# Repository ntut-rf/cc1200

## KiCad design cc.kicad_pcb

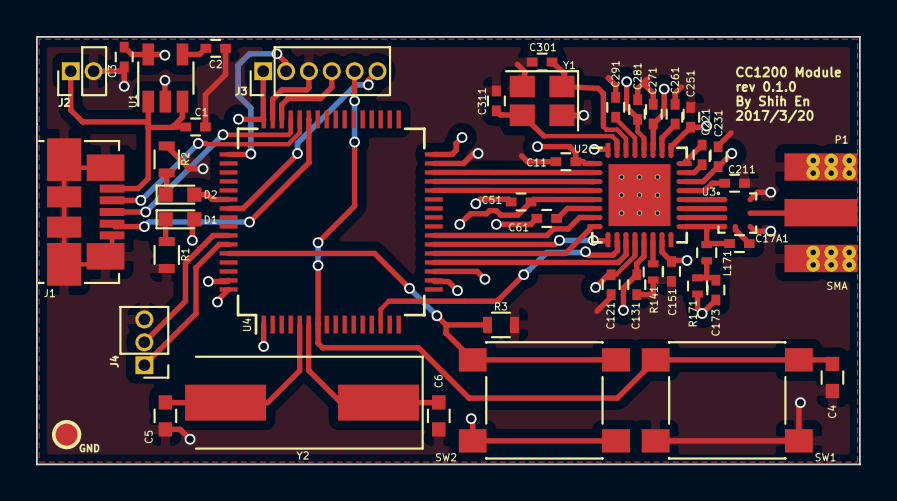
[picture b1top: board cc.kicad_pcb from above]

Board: 4 copper layers, 45.7 x 23.7 mm, 46 parts (0 on the bottom side), 43 nets.

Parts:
C1: 0.1uF; C_0402
C2: 0.01uF; C_0402
C3: 2.2uF; C_0402
C4: 0.1uF/25V; C_0603
C5, C6: 20pF; C_0603
C11, C51, C121, C131, C151, C221, C251, C261, C271, C281, C291: 47nF; C_0402
C17A1: 100pF; C_0402
C61: 220nF; C_0402
C173: 56pF; C_0402
C211: 10nF; C_0402
C231: 1.5nF; C_0402
C301, C311: 15pF; C_0402
D1: LED_PWR; LED_0603
D2: LED_TEST; LED_0603
GND: GND; TESTPOINT-50MIL
J1: USB_OTG; USB_Micro-B_Molex_47346-0001
J2: CONN_PWR; Pin_Header_Straight_1x02_Pitch1.27mm
J3: CONN_DEBUG; Pin_Header_Straight_1x06_Pitch1.27mm
J4: CONN_USART; Pin_Header_Straight_1x03_Pitch1.27mm
L171: 56nH; L_0402
P1: SMA; SMA-EDGE
R1, R2: 200; R_0603
R3: 10k; R_0603
R141: 56k; R_0402
R171: 18; R_0402
SW1, SW2: SW_Push; SW_SPST_PTS645
U1: TPS79333; TSOT-23-5
U2: CC1200
U3: BALF-112X-02D3
U4: STM32L475RC; LQFP-64_10x10mm_Pitch0.5mm
Y1: 40MHz; NX3225SA-40M-EXS00A-CS03880
Y2: 8MHz(16pF); Crystal_SMD_HC49-SD

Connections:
+5V: C1.1, J1.1, J2.1, U1.1, U1.3
CC_GPIO0: U2.10, U4.14
CC_GPIO2: U2.4, U4.28
CC_GPIO3: U2.3, U4.29
CC_MISO: U2.9, U4.22
CC_MOSI: U2.7, U4.23
CC_NSS: U2.11, U4.20
CC_RESET_N: U2.2, U4.30
CC_SCLK: U2.8, U4.21
GND: C1.2, C2.2, C3.2, C4.1, C5.2, C6.2, C11.2, C51.2, C61.2, C121.2, C131.2, C151.2, C211.2, C221.2, C251.2, C261.2, C271.2, C281.2, C291.2, C301.2, C311.2, J1.5, J1.6, J2.2, J3.3, J4.3, P1.2, R1.2, R2.1, R3.2, R141.2, SW1.2, U1.2, U2.32, U2.33, U3.A1, U3.E1, U4.18, U4.31, U4.47, U4.63, Y1.2, Y1.4
NRST: C4.2, J3.5, SW1.1, U4.7
unnamed: C2.1, U1.4
unnamed: C5.1, U4.5, Y2.2
unnamed: C6.1, U4.6, Y2.1
unnamed: C17A1.1, L171.1, U2.17, U3.E3
unnamed: C17A1.2, U3.E2
unnamed: C61.1, U2.6
unnamed: C173.1, L171.2, R171.1
unnamed: C211.1, U2.21
unnamed: C231.1, U2.24
unnamed: C231.2, U2.23
unnamed: C261.1, U2.26
unnamed: C291.1, U2.29
unnamed: C301.1, U2.30, Y1.1
unnamed: C311.1, U2.31, Y1.3
unnamed: D1.1, R1.1
unnamed: D2.1, R2.2
unnamed: D2.2, U4.54
unnamed: P1.1, U3.C1
unnamed: R3.1, SW2.2, U4.60
unnamed: R141.1, U2.14
unnamed: U2.18, U3.D3
unnamed: U2.19, U3.B3
unnamed: U2.20, U3.A3
SWCLK: J3.2, U4.49
SWDIO: J3.4, U4.46
SWO: J3.6, U4.55
USART_RX: J4.1, U4.59
USART_TX: J4.2, U4.58
USB_DM: J1.2, U4.44
USB_DP: J1.3, U4.45
USB_ID: J1.4, U4.43
VDD: C3.1, C11.1, C51.1, C121.1, C131.1, C151.1, C173.2, C221.1, C251.1, C271.1, C281.1, D1.2, J3.1, R171.2, SW2.1, U1.5, U2.1, U2.5, U2.12, U2.13, U2.15, U2.22, U2.25, U2.27, U2.28, U4.1, U4.19, U4.32, U4.48, U4.64

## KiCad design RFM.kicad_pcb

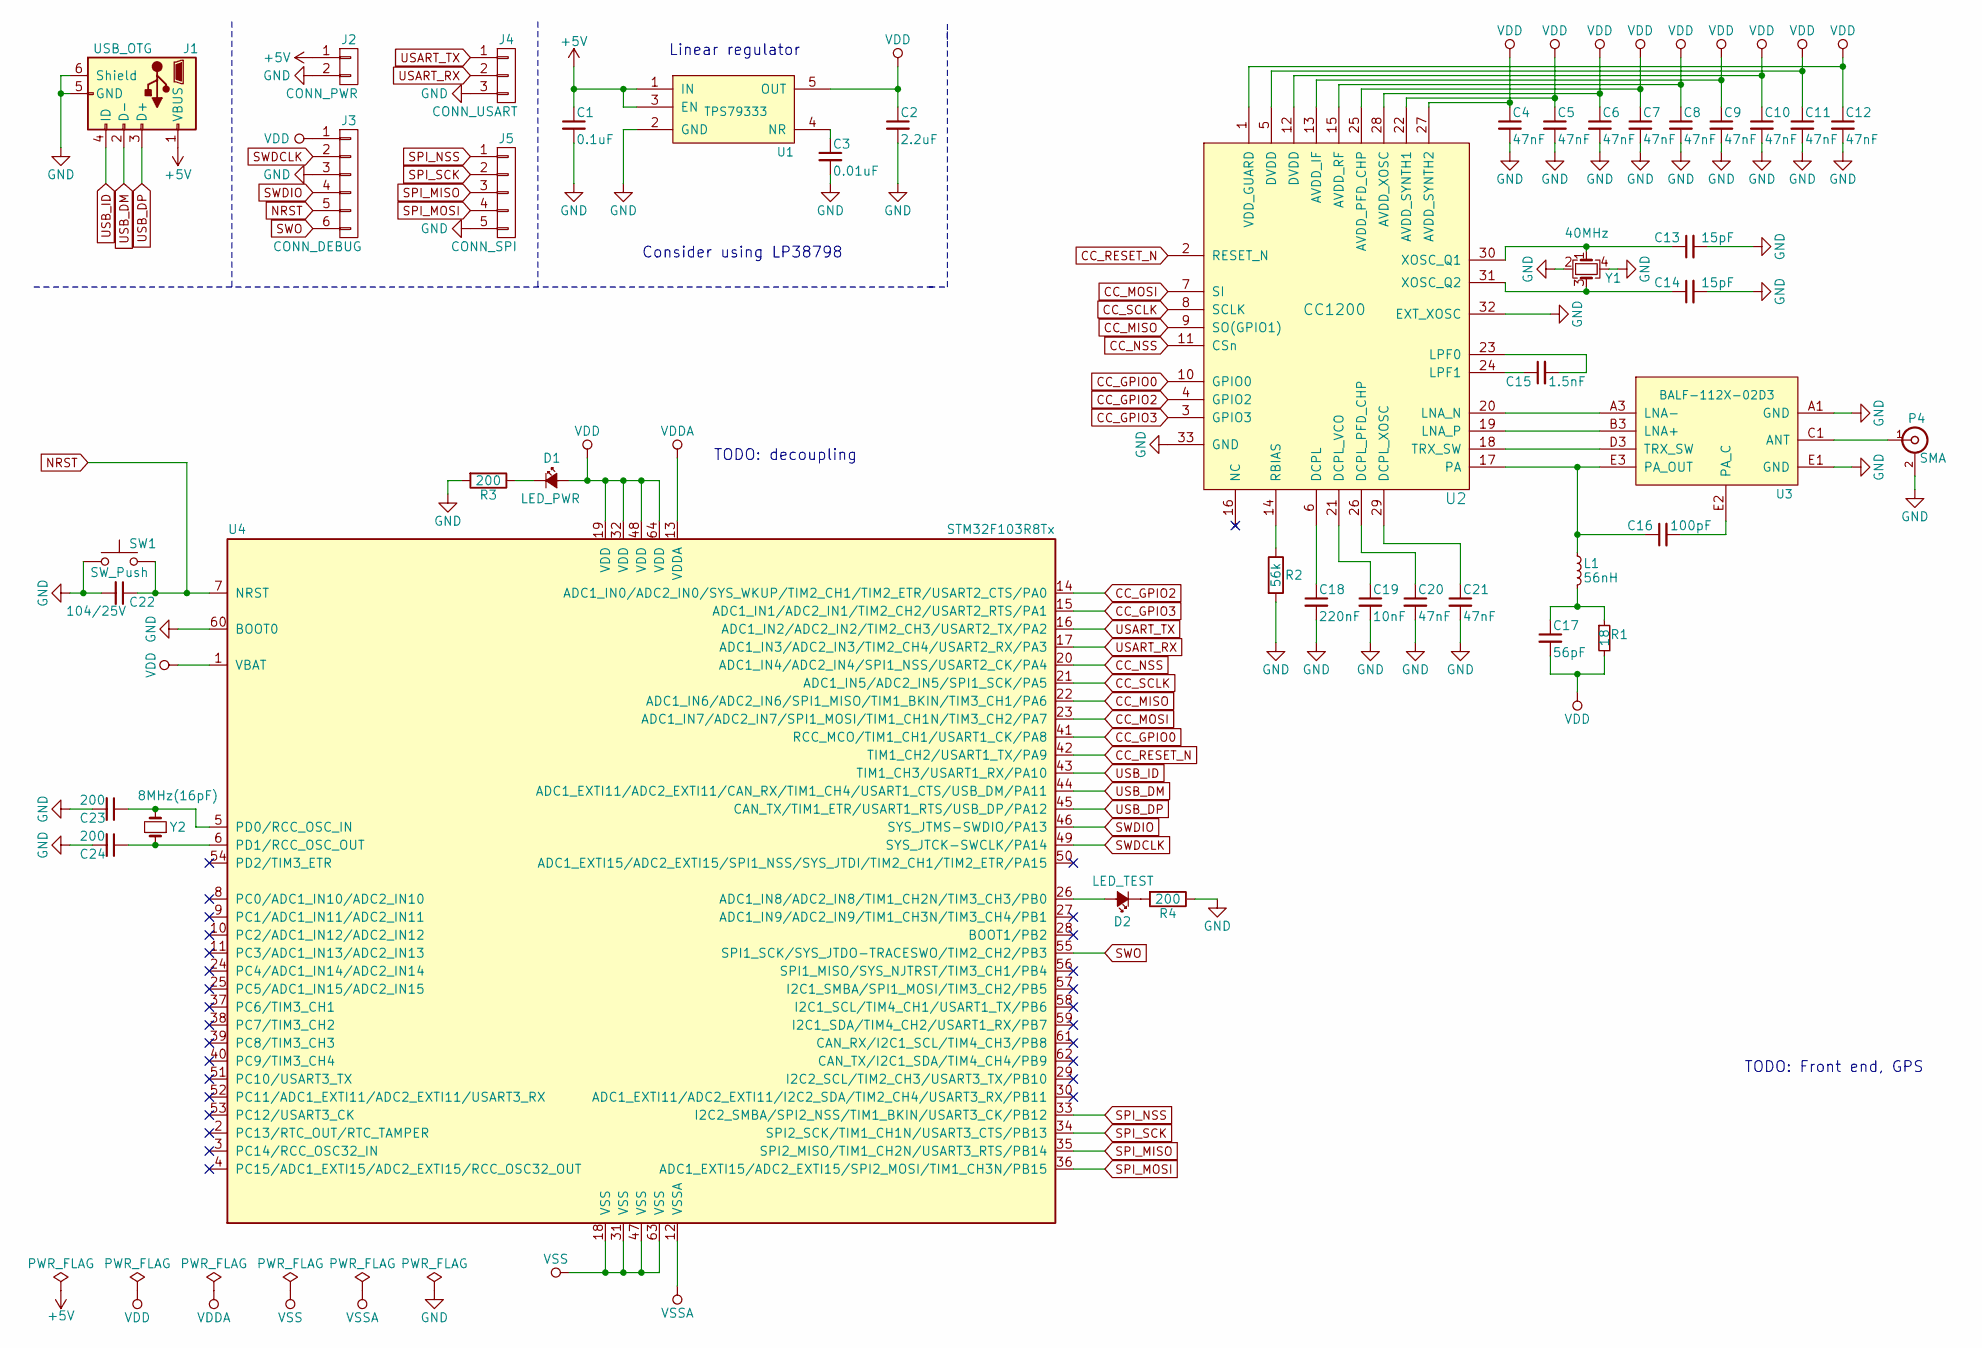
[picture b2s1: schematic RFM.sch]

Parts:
C1: 0.1uF; C_0402
C2: 2.2uF; C_0402
C3: 0.01uF; C_0402
C4, C5, C6, C7, C8, C9, C10, C11, C12, C20, C21: 47nF; C_0402
C13, C14: 15pF; C_0402
C15: 1.5nF; C_0402
C16: 100pF; C_0402
C17: 56pF; C_0402
C18: 220nF; C_0402
C19: 10nF; C_0402
C22: 104/25V; C_0603
C23, C24: 200; C_0603
D1: LED_PWR; LED_0603
D2: LED_TEST; LED_0603
J1: USB_OTG; USB_Micro-B_Molex_47346-0001
J2: CONN_PWR; Pin_Header_Angled_1x02_Pitch2.54mm
J3: CONN_DEBUG; Pin_Header_Angled_1x06_Pitch2.54mm
J4: CONN_USART; Pin_Header_Angled_1x03_Pitch2.54mm
J5: CONN_SPI; Pin_Header_Angled_1x05_Pitch2.54mm
L1: 56nH; L_0402
P4: SMA; SMA-EDGE
R1: 18; R_0402
R2: 56k; R_0402
R3, R4: 200; R_0603
SW1: SW_Push; SW_SPST_PTS645
U1: TPS79333; TSOT-23-5
U2: CC1200
U3: BALF-112X-02D3
U4: STM32F103R8Tx; LQFP-64_10x10mm_Pitch0.5mm
Y1: 40MHz; NX3225SA-40M-EXS00A-CS03880
Y2: 8MHz(16pF)

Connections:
+5V: C1.1, J1.1 (VBUS), J2.1, U1.1 (IN), U1.3 (EN)
CC_GPIO0: U2.10 (GPIO0), U4.41 (RCC_MCO/TIM1_CH1/USART1_CK/PA8)
CC_GPIO2: U2.4 (GPIO2), U4.14 (ADC1_IN0/ADC2_IN0/SYS_WKUP/TIM2_CH1/TIM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)
CC_GPIO3: U2.3 (GPIO3), U4.15 (ADC1_IN1/ADC2_IN1/TIM2_CH2/USART2_RTS/P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)
CC_MISO: U2.9 (SO(GPIO1)), U4.22 (ADC1_IN6/ADC2_IN6/SPI1_MISO/TIM1_BKIN/T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)
CC_MOSI: U2.7 (SI), U4.23 (ADC1_IN7/ADC2_IN7/SPI1_MOSI/TIM1_CH1N/T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)
CC_NSS: U2.11 (CSn), U4.20 (ADC1_IN4/ADC2_IN4/SPI1_NSS/USART2_CK/PA4)
CC_RESET_N: U2.2 (RESET_N), U4.42 (TIM1_CH2/USART1_TX/PA9)
CC_SCLK: U2.8 (SCLK), U4.21 (ADC1_IN5/ADC2_IN5/SPI1_SCK/PA5)
GND: C1.2, C2.2, C3.2, C4.2, C5.2, C6.2, C7.2, C8.2, C9.2, C10.2, C11.2, C12.2, C13.2, C14.2, C18.2, C19.2, C20.2, C21.2, C22.2, C23.2, C24.2, J1.5 (GND), J1.6 (Shield), J2.2, J3.3, J4.3, J5.5, P4.2 (Ext), R2.2, R3.2, R4.1, SW1.1, U1.2 (GND), U2.32 (EXT_XOSC), U2.33 (GND), U3.A1 (GND), U3.E1 (GND), U4.60 (BOOT0), Y1.2, Y1.4
NRST: C22.1, J3.5, SW1.2, U4.7 (NRST)
unnamed: C3.1, U1.4 (NR)
unnamed: C13.1, U2.30 (XOSC_Q1), Y1.1
unnamed: C14.1, U2.31 (XOSC_Q2), Y1.3
unnamed: C15.1, U2.24 (LPF1)
unnamed: C15.2, U2.23 (LPF0)
unnamed: C16.1, L1.1, U2.17 (PA), U3.E3 (PA_OUT)
unnamed: C16.2, U3.E2 (PA_C)
unnamed: C17.1, L1.2, R1.1
unnamed: C18.1, U2.6 (DCPL)
unnamed: C19.1, U2.21 (DCPL_VCO)
unnamed: C20.1, U2.26 (DCPL_PFD_CHP)
unnamed: C21.1, U2.29 (DCPL_XOSC)
unnamed: C23.1, U4.5 (PD0/RCC_OSC_IN), Y2.2
unnamed: C24.1, U4.6 (PD1/RCC_OSC_OUT), Y2.1
unnamed: D1.1 (K), R3.1
unnamed: D2.1 (K), R4.2
unnamed: D2.2 (A), U4.26 (ADC1_IN8/ADC2_IN8/TIM1_CH2N/TIM3_CH3/PB0)
unnamed: P4.1 (In), U3.C1 (ANT)
unnamed: R2.1, U2.14 (RBIAS)
unnamed: U2.18 (TRX_SW), U3.D3 (TRX_SW)
unnamed: U2.19 (LNA_P), U3.B3 (LNA+)
unnamed: U2.20 (LNA_N), U3.A3 (LNA-)
SPI_MISO: J5.3, U4.35 (SPI2_MISO/TIM1_CH2N/USART3_RTS/PB14)
SPI_MOSI: J5.4, U4.36 (ADC1_EXTI15/ADC2_EXTI15/SPI2_MOSI/TIM1_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)
SPI_NSS: J5.1, U4.33 (I2C2_SMBA/SPI2_NSS/TIM1_BKIN/USART3_CK/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)
SPI_SCK: J5.2, U4.34 (SPI2_SCK/TIM1_CH1N/USART3_CTS/PB13)
SWDCLK: J3.2, U4.49 (SYS_JTCK-SWCLK/PA14)
SWDIO: J3.4, U4.46 (SYS_JTMS-SWDIO/PA13)
SWO: J3.6, U4.55 (SPI1_SCK/SYS_JTDO-TRACESWO/TIM2_CH2/PB3)
USART_RX: J4.2, U4.17 (ADC1_IN3/ADC2_IN3/TIM2_CH4/USART2_RX/PA3)
USART_TX: J4.1, U4.16 (ADC1_IN2/ADC2_IN2/TIM2_CH3/USART2_TX/PA2)
USB_DM: J1.2 (D-), U4.44 (ADC1_EXTI11/ADC2_EXTI11/CAN_RX/TIM1_CH4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)
USB_DP: J1.3 (D+), U4.45 (CAN_TX/TIM1_ETR/USART1_RTS/USB_DP/PA12)
USB_ID: J1.4 (ID), U4.43 (TIM1_CH3/USART1_RX/PA10)
VDD: C2.1, C4.1, C5.1, C6.1, C7.1, C8.1, C9.1, C10.1, C11.1, C12.1, C17.2, D1.2 (A), J3.1, R1.2, U1.5 (OUT), U2.1 (VDD_GUARD), U2.5 (DVDD), U2.12 (DVDD), U2.13 (AVDD_IF), U2.15 (AVDD_RF), U2.22 (AVDD_SYNTH1), U2.25 (AVDD_PFD_CHP), U2.27 (AVDD_SYNTH2), U2.28 (AVDD_XOSC), U4.1 (VBAT), U4.19 (VDD), U4.32 (VDD), U4.48 (VDD), U4.64 (VDD)
VSS: U4.18 (VSS), U4.31 (VSS), U4.47 (VSS), U4.63 (VSS)

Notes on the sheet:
Linear regulator
TODO: Front end, GPS
Consider using LP38798
TODO: decoupling

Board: 2 copper layers, 44 parts (0 on the bottom side), 47 nets, no tracks yet.

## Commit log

2017-03-15 Start drawing CC1200 footprint
2017-03-15 Update footprint assignments
2017-03-16 CC1200 footprint
2017-03-16 Balun footprint
2017-03-17 Update footprints
2017-03-17 Rename
2017-03-18 Use STM32L475RC
2017-03-18 Footprint spreadout
2017-03-18 PCB layout WIP
2017-03-20 Component layout etc.
2017-03-20 Polishing
2017-03-20 Layout
2017-03-21 Pre v0.1.0
